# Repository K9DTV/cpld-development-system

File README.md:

> **Archived — final / last release.** This project is complete and frozen. Issues and PRs are not expected; the tree is the historical record.

# CPLD Development System

A hand-designed Altera MAX 7000AE/S CPLD development board and the digital labs built on it — from Lake Washington Institute of Technology **Electronics 211** (2017–2018), by **James Burney (K9DTV)**.

This repository packs the PCB design, fabrication outputs, board photos, project write-ups, and a Quartus calculator experiment that targeted the board.

<p align="center">
  
  &nbsp;
  
</p>

<p align="center"><em>Left (white / Ver2): board pictured with the <strong>MAX 7000S</strong> <strong>5&nbsp;V</strong> CPLD setup. Right (green): Ver1-style build.</em></p>

## What this board is

The goal was a durable **printed** CPLD trainer for the same class work that started on a hand-wired prototype: DIP switches in, dual hexadecimal TIL311-style displays out, on-board clock, and a standard JTAG/ByteBlaster programming header.

Two PCB revisions shipped:

| Version | How to spot it | Notes |
|--------|----------------|--------|
| **Ver1** | No silkscreen | Used for most lab examples in the docs |
| **Ver2** | Has silkscreen | Three display-control pins remapped (see pin table below) |

Power: about **6.5 V–12 V** input (prefer the low end; regulators get hot). Current-limit around **160 mA** when using a bench supply. Drive each display **decimal point with an open-drain** buffer so the DP turns fully off.

### MAX 7000S (5 V) vs MAX 7000AE (3.3 V)

Same PLCC-44 socket and the same lab/pin idea. The difference is supply voltage / family:

| Family | Example parts | Core / I/O | Notes |
|--------|---------------|------------|--------|
| **MAX 7000S** | EPM7032, **EPM7064S** | **5 V** | White board photo; use `Calculator-full-5v` |
| **MAX 7000AE** | EPM7032AE, **EPM7064AE** | **3.3 V** | Use `Calculator-full-3v3` |

Same calculator logic / pinout in both folders — pick the build that matches the CPLD voltage on the board. Do not mix a 5 V part with a 3.3 V rail (or the reverse) without checking VCCIO/VCCINT wiring.

Supported CPLDs (PLCC-44):

- **EPM7032** / **EPM7032AE** (32 macrocells) — display/switch / board-test labs  
- **EPM7064S** (64 MC, **5 V**) — full calculator (`calulator/Calculator-full-5v/`)  
- **EPM7064AE** (64 MC, **3.3 V**) — full calculator (`calulator/Calculator-full-3v3/`)

## Repository layout

```
.
├── README.md
├── cpld-white.jpg / cpld-green.jpg   # Assembled boards
├── cpld-pcb.png / cpld-sch.png       # Layout / schematic views
├── PCB-files/
│   ├── cpld/                         # KiCad schematic + PCB (legacy KiCad 4 era)
│   └── CLPD-grb/                     # Gerbers + drill for fab
├── calulator/                        # Quartus II projects (folder spelling preserved)
│   ├── Calculator-full-5v/           # Full calculator — EPM7064S / 5 V
│   ├── Calculator-full-3v3/          # Full calculator — EPM7064AE / 3.3 V
│   ├── board test/                   # Board bring-up
│   ├── board-test-2/                 # Switch / display exercise (32 MC)
│   └── boardtest3/                   # Follow-on board test (uses board-test-2 BDFs)
├── project docs/                     # Word write-ups + markdown/ previews for GitHub
└── homework/                         # Class notes (ELEC 211 Ch. 4)
```

Folder and filename spellings (`calulator`, `CLPD-grb`, spaces in `project docs`) match the original archive on purpose.

## Hardware pin map

DIP switches are active-low (closed = logic 0). Most designs invert them in the CPLD so “switch ON” reads as a 1 in the logic.

| Function | Ver1 CPLD pin | Ver2 CPLD pin |
|----------|---------------|---------------|
| DIP SW 1–12 | 4, 5, 6, 8, 9, 12, 11, 14, 16, 17, 19, 18 | same |
| Clock (~66.6 kHz from 555) | 24 | 24 |
| Display A / B / C / D | 27 / 25 / 26 / 28 | same |
| Display Blank | 29 | 29 |
| Right Latch | **31** | **33** |
| Left Latch | **33** | **36** |
| Right DP | 34 | 34 |
| Left DP | **36** | **31** |

Programming-header pins follow the usual Altera JTAG layout (not duplicated in the table).

### Major bill of materials (either revision)

| Ref | Part | Notes |
|-----|------|--------|
| IC1 | EPM7032 / EPM7064S (5 V) or EPM7064AE (3.3 V), PLCC-44 | 64 MC for full calculator |
| U1–U2 | LM1117-5.0 | 5 V rails |
| U3 | LM1117-3.3 | CPLD I/O / core as wired |
| U4 | LM555 | ~66.6 kHz board clock |
| U5–U6 | TIL311 (or DIS1417) | Hex displays (hard to source; eBay) |
| SW1 | 12-position DIP slide | Active-low inputs |
| RN1 / RN2 | 10 kΩ SIP arrays | Pull-ups |
| J2 | 2×5 header | Programming |

Full Digi-Key / Mouser part numbers are in `project docs/pcb document and cpld project.docx`.

## Labs and example designs

Documented in `project docs/`:

1. **Board bring-up** — display blank/latch behavior, 555 clock divider blinking both DPs (~1 Hz after ÷65536).  
2. **Priority encoder** — exercises all DIP switches into the hex displays (BCD).  
3. **Calculator** (needs **64 MC** device) — mode select on SW11/SW12:
   - SW11=0, SW12=0 → **min/max** (7485-style compare; DPs show a swap)
   - SW11=0, SW12=1 → **add**
   - SW11=1, SW12=1 → **subtract** (borrow aware)
   - SW11=1, SW12=0 → **multiply**  
   Full builds: `Calculator-full-5v/` (**EPM7064S**, 5 V) and `Calculator-full-3v3/` (**EPM7064AE**, 3.3 V).
4. **Two-digit counter** — final-style exercise on the same pinout (`two digit counter cpld project.docx`).
5. **Hand-wired prototype** — earlier 7000-series socket board used for Ch. 4 / Ch. 7 (`211 build board.docx`).

## Quartus project (`calulator/`)

Intel/Altera **Quartus II** block-diagram labs. Folder name spelling `calulator` is preserved. The calculator top entity is named **`Calculator`**.

### Full calculator (two voltage builds)

| Folder | Device | I/O standard | Fit | Use when |
|--------|--------|--------------|-----|----------|
| `Calculator-full-5v/` | **EPM7064SLC44-10** (MAX7000S) | TTL (5 V) | 60 / 64 MC | 5 V CPLD (white board photo setup) |
| `Calculator-full-3v3/` | **EPM7064AELC44-10** (MAX7000AE) | 3.3-V LVTTL | 60 / 64 MC | 3.3 V AE CPLD |

Each folder has its own `Calculator.qpf`, BDFs/BSFs, `Calculator.pof`, and reports. Ver2 display pins (latch_R=33, latch_L=36, Left_DP=31). Open the folder that matches the chip on the board.

### Board tests

| Folder | Role |
|--------|------|
| `board test/` | Bring-up (`boardtest.qpf`, `.pof` included) |
| `board-test-2/` | Switch/display lab (`board-test-2.qpf`, EPM7032AE, `.pof` included) |
| `boardtest3/` | Later board test (`test3.qpf`; BDFs referenced from `../board-test-2/`) |

Suggested tools: **Quartus II 13.0 SP1** (or 17.1 Lite) with a USB-Blaster.

## KiCad / fabrication (`PCB-files/`)

- `PCB-files/cpld/` — schematic (`.sch`), board (`.kicad_pcb`), netlist, project (KiCad 4-style `.pro`).  
- `PCB-files/CLPD-grb/` — Gerber layers (F/B Cu, mask, silk, edge cuts) and `cpld.drl`.

Open with a modern KiCad via the legacy importer, or send the Gerbers straight to a fab.

<p align="center">
  
  &nbsp;
  
</p>

## Documentation (`project docs/`)

Original Word write-ups stay in the folder (provenance). **GitHub-readable Markdown previews** (text extracted from those `.docx` files) live under [`project docs/markdown/`](project%20docs/markdown/):

| Word (original) | Markdown preview | Contents |
|-----------------|------------------|----------|
| `211 build board.docx` | [211-build-board.md](project%20docs/markdown/211-build-board.md) | Hand-wired prototype + Ch. 7 calculator path |
| `pcb document and cpld project.docx` | [pcb-document-and-cpld-project.md](project%20docs/markdown/pcb-document-and-cpld-project.md) | Ver1/Ver2 PCB, pin map, BOM, calculator labs |
| `two digit counter cpld project.docx` | [two-digit-counter-cpld-project.md](project%20docs/markdown/two-digit-counter-cpld-project.md) | Counter lab on the PCB |
| `211 PROJECT.docx` | [211-project.md](project%20docs/markdown/211-project.md) | Course project write-up |
| `211 final.docx` | [211-final.md](project%20docs/markdown/211-final.md) | Final write-up |

Course context: **Lake Washington Institute of Technology**, Electronics 211, instructor **Professor Peter Welty**.

## License / provenance

MIT -- see [LICENSE](LICENSE). Personal educational hardware and reports by James Burney (K9DTV). Course homework notes in `homework/` are included as archived class material. Altera/Intel tool output remains under their respective license terms.

Site / project page: [k9dtv.com/project-cpld.html](https://k9dtv.com/project-cpld.html) · GitHub: [K9DTV/cpld-development-system](https://github.com/K9DTV/cpld-development-system)

---

*Archived from the original CPLD development-system materials (2017–2018) and published as a public K9DTV project.*

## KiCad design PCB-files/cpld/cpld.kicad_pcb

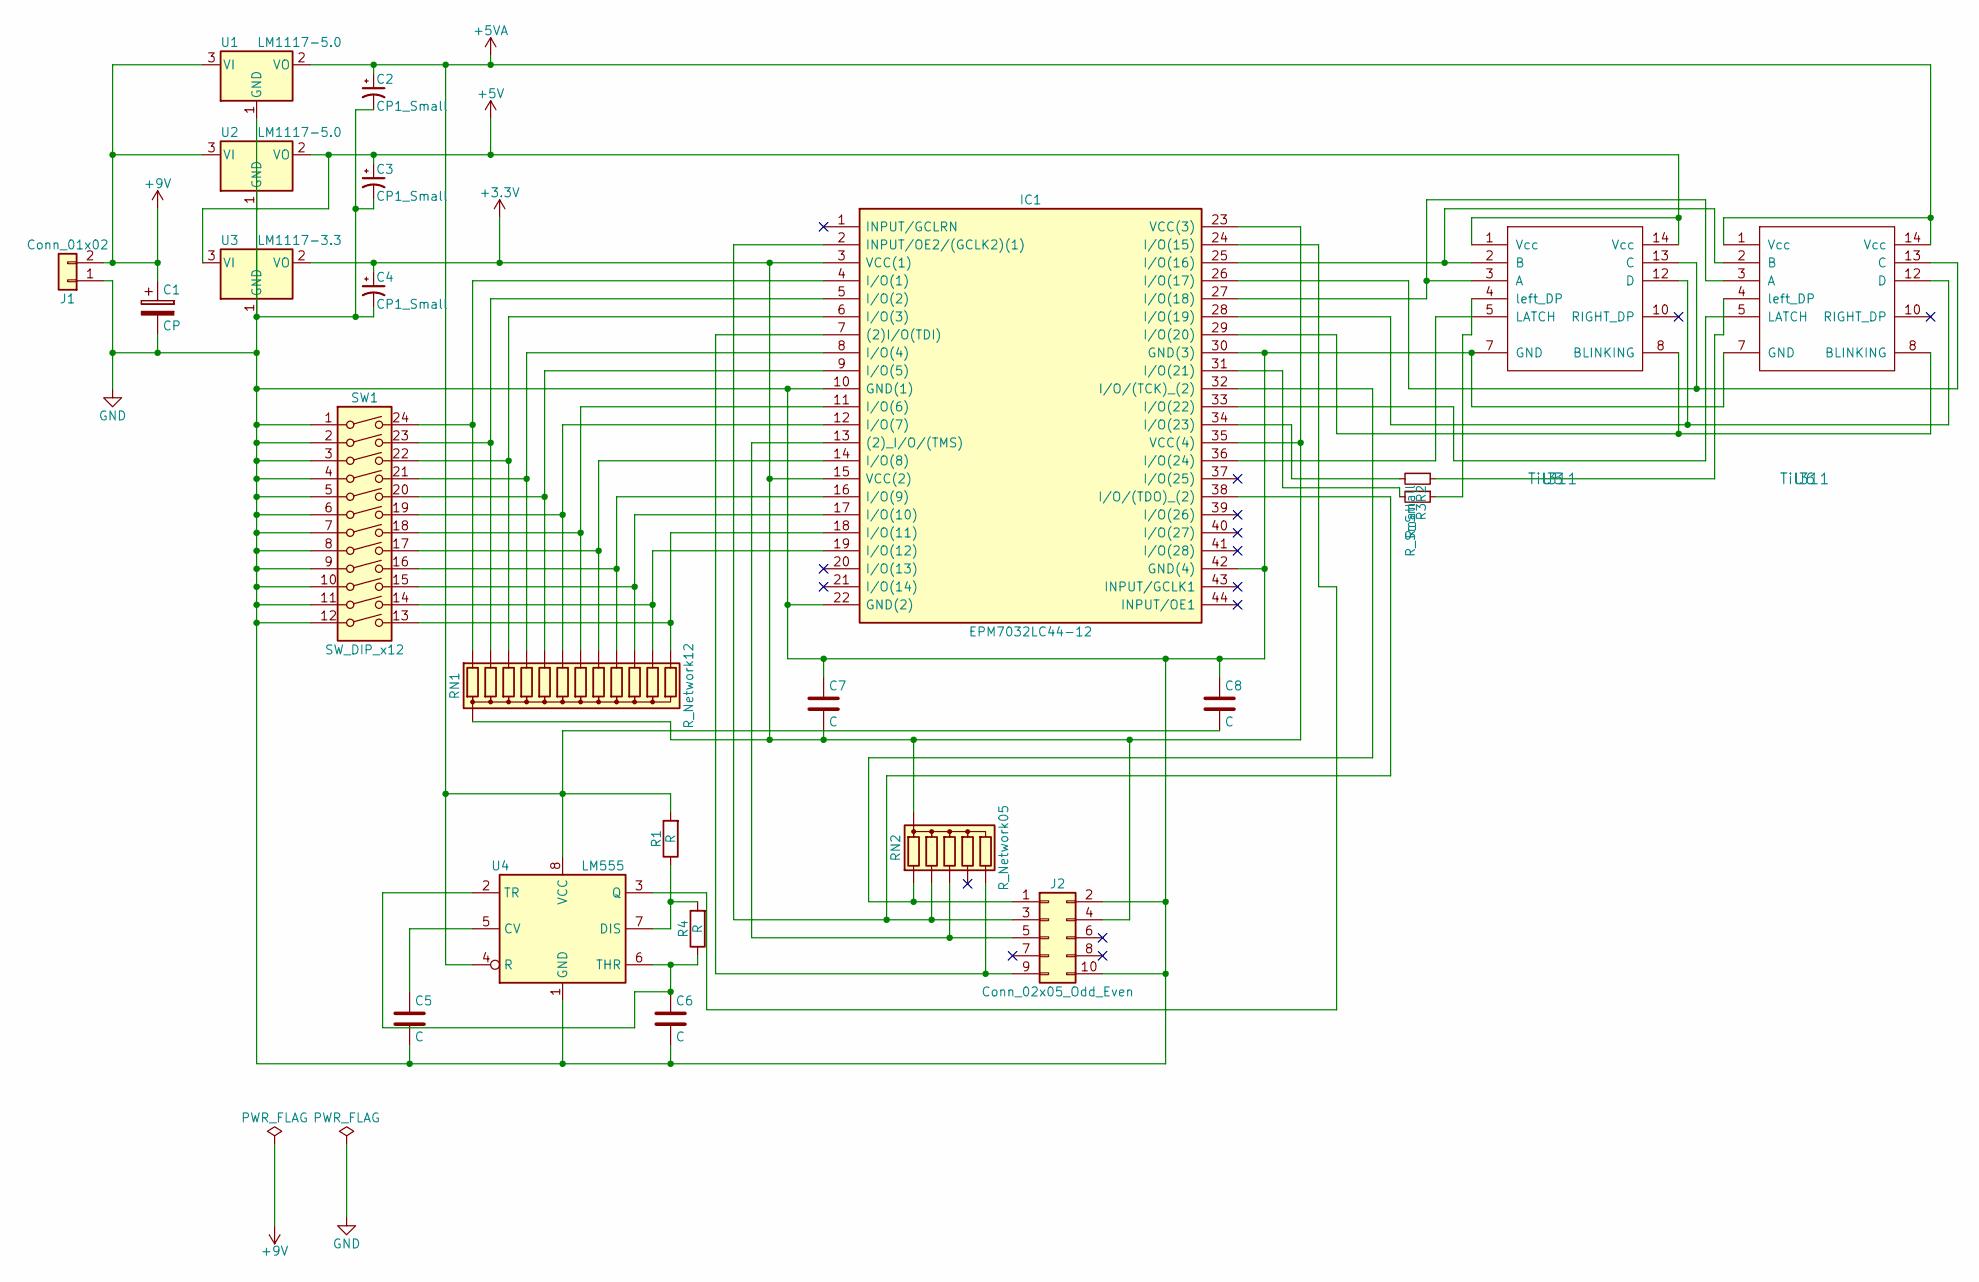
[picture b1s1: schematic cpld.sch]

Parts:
C1: CP; CP_Radial_D5.0mm_P2.50mm
C2, C3, C4: CP1_Small; CP_Radial_D5.0mm_P2.50mm
C5, C6, C7, C8: C; C_Axial_L3.8mm_D2.6mm_P7.50mm_Horizontal
IC1: EPM7032LC44-12; PLCC44; Manufacturer_Part_Number EPM7032LC44-12
J1: Conn_01x02; Pin_Header_Straight_1x02_Pitch2.54mm
J2: Conn_02x05_Odd_Even; Pin_Header_Straight_2x05_Pitch2.54mm
R1, R4: R; R_Axial_DIN0204_L3.6mm_D1.6mm_P7.62mm_Horizontal
R2, R3: R_Small; R_Axial_DIN0204_L3.6mm_D1.6mm_P7.62mm_Horizontal
RN1: R_Network12; Socket_Strip_Straight_1x13_Pitch2.54mm
RN2: R_Network05; Socket_Strip_Straight_1x06_Pitch2.54mm
SW1: SW_DIP_x12; SW_DIP_x12_W7.62mm_Slide
U1, U2: LM1117-5.0; TO-220
U3: LM1117-3.3; TO-220
U4: LM555; DIP-8_W7.62mm
U5, U6: Til311; DIP-14_W7.62mm

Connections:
+3V3: C4.1, C7.2, IC1.3 (VCC(1)), IC1.15 (VCC(2)), IC1.23 (VCC(3)), IC1.35 (VCC(4)), J2.4, RN1.1 (common), RN2.1 (common), U3.2 (VO)
+5V: C3.1, U2.2 (VO), U3.3 (VI), U5.1 (Vcc), U5.14 (Vcc)
+5VA: C2.1, C8.2, R1.2, U1.2 (VO), U4.4 (R), U4.8 (VCC), U6.1 (Vcc), U6.14 (Vcc)
+9V: C1.1, J1.2, U1.3 (VI), U2.3 (VI)
GND: C1.2, C2.2, C3.2, C4.2, C5.2, C6.2, C7.1, C8.1, IC1.10 (GND(1)), IC1.22 (GND(2)), IC1.30 (GND(3)), IC1.42 (GND(4)), J1.1, J2.2, J2.10, SW1.1, SW1.2, SW1.3, SW1.4, SW1.5, SW1.6, SW1.7, SW1.8, SW1.9, SW1.10, SW1.11, SW1.12, U1.1 (GND), U2.1 (GND), U3.1 (GND), U4.1 (GND), U5.7 (GND), U6.7 (GND)
unnamed: C5.1, U4.5 (CV)
unnamed: C6.1, R4.1, U4.2 (TR), U4.6 (THR)
unnamed: IC1.2 (INPUT/OE2/(GCLK2)(1)), IC1.38 (I/O/(TDO)_(2)), J2.3, RN2.3 (R2)
unnamed: IC1.4 (I/O(1)), RN1.2 (R1), SW1.24
unnamed: IC1.5 (I/O(2)), RN1.3 (R2), SW1.23
unnamed: IC1.6 (I/O(3)), RN1.4 (R3), SW1.22
unnamed: IC1.7 ((2)I/O(TDI)), J2.9, RN2.6 (R5)
unnamed: IC1.8 (I/O(4)), RN1.5 (R4), SW1.21
unnamed: IC1.9 (I/O(5)), RN1.6 (R5), SW1.20
unnamed: IC1.11 (I/O(6)), RN1.8 (R7), SW1.18
unnamed: IC1.12 (I/O(7)), RN1.7 (R6), SW1.19
unnamed: IC1.13 ((2)_I/O/(TMS)), J2.5, RN2.4 (R3)
unnamed: IC1.14 (I/O(8)), RN1.9 (R8), SW1.17
unnamed: IC1.16 (I/O(9)), RN1.10 (R9), SW1.16
unnamed: IC1.17 (I/O(10)), RN1.11 (R10), SW1.15
unnamed: IC1.18 (I/O(11)), RN1.13 (R12), SW1.13
unnamed: IC1.19 (I/O(12)), RN1.12 (R11), SW1.14
unnamed: IC1.24 (I/O(15)), U4.3 (Q)
unnamed: IC1.25 (I/O(16)), U5.2 (B), U6.2 (B)
unnamed: IC1.26 (I/O(17)), U5.13 (C), U6.13 (C)
unnamed: IC1.27 (I/O(18)), U5.3 (A), U6.3 (A)
unnamed: IC1.28 (I/O(19)), U5.12 (D), U6.12 (D)
unnamed: IC1.29 (I/O(20)), U5.8 (BLINKING), U6.8 (BLINKING)
unnamed: IC1.31 (I/O(21)), R3.2
unnamed: IC1.32 (I/O/(TCK)_(2)), J2.1, RN2.2 (R1)
unnamed: IC1.33 (I/O(22)), U6.5 (LATCH)
unnamed: IC1.34 (I/O(23)), R2.2
unnamed: IC1.36 (I/O(24)), U5.5 (LATCH)
unnamed: R1.1, R4.2, U4.7 (DIS)
unnamed: R2.1, U6.4 (left_DP)
unnamed: R3.1, U5.4 (left_DP)

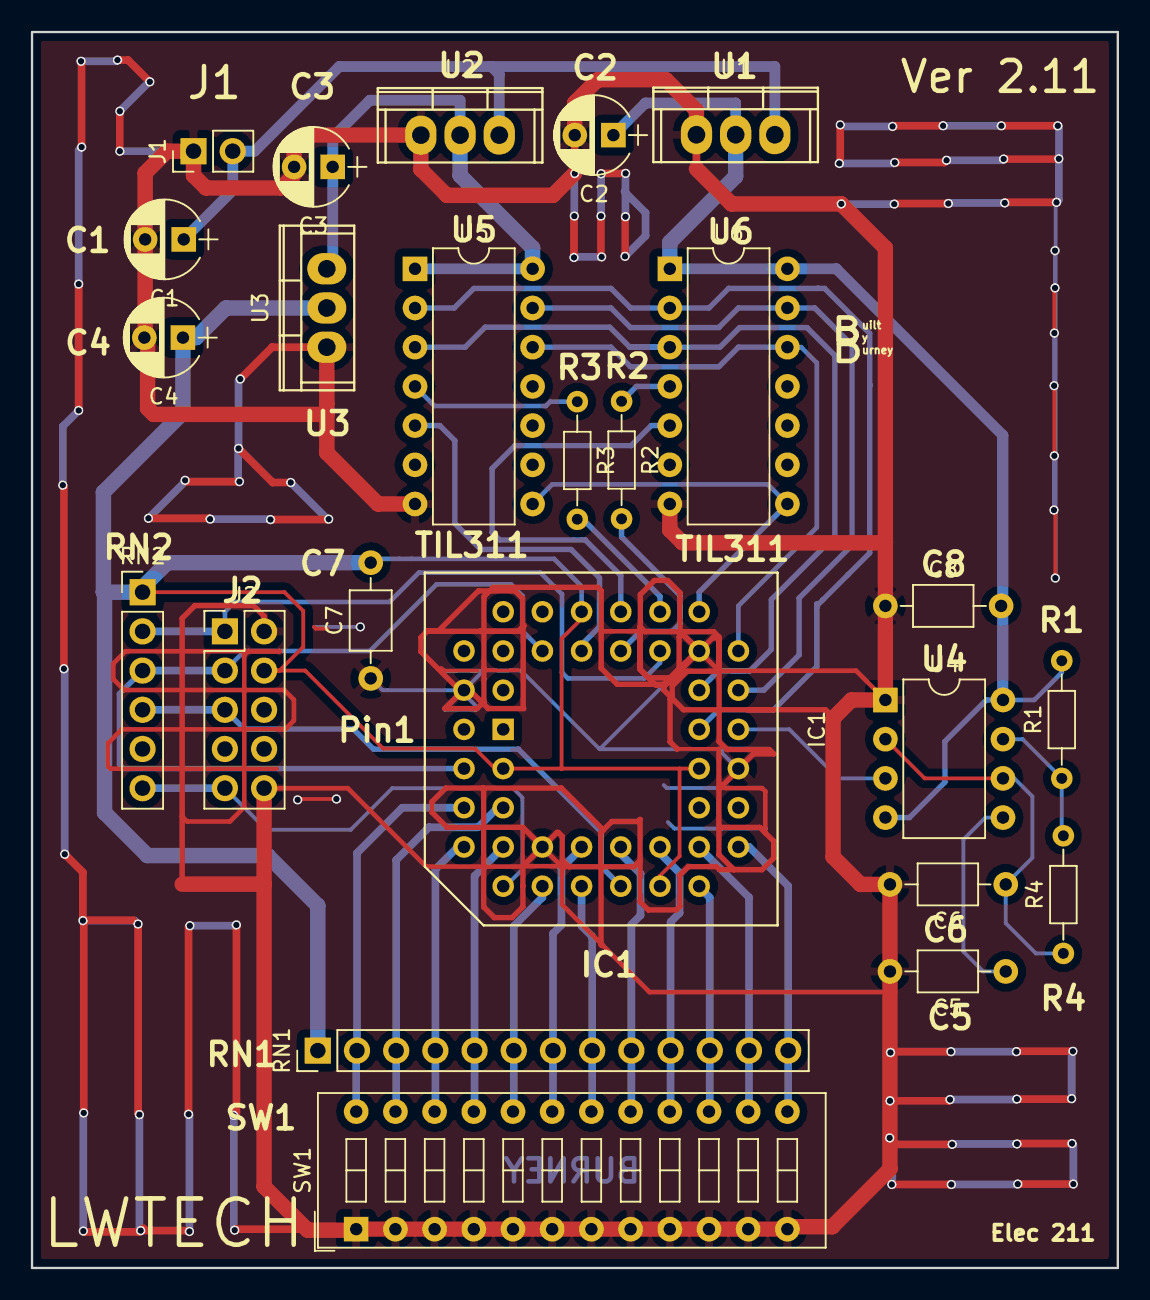
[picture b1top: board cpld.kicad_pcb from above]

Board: 2 copper layers, 70.4 x 80.1 mm, 24 parts (0 on the bottom side), 36 nets.

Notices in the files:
README.md:
License: MIT
